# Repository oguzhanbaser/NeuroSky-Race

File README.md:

# NeuroSky-Race

### If you want to use STM32F103 with this project, you should choose "stm32" branch. 

In this application you can use your attention level to control car speed. Application designed for two racers. You will need following items for this project:

    - NeuroSky Mindwave Sensors * 2
    - Arduino (Nano in this example but can be different) * 2
    - IRFZ44N Mosfet * 2
    - HC-05 Bluetooth * 2
    - Slot Car Track
    - MZ-80 (Optional) * 2
    - FTDI Converter(Optional) * 2
    - PC (Optional)

### First-Upload
For the first UPLOAD you have to uncomment this line in "configuration.h". Next time you can comment it again. This line saves speed levels to EEPROM. 

```arduino

//#define WRITE_EEPROM 

```

### Interface
If you want to use NodeJs web interface you will need a PC to run server. Connect two Arduino with USB cable to PC and set port names in "server.js"

```javascript
var portName1 = "COM5";         //if you use using Linux /dev/tty***
var portName2 = "COM13";        //if you are using Linux /dev/tty***
```

```sh

$ cd Web-Interface
$ npm install
$ node server.js

```

</img>

### Software Serial
You can use FTDI converter or direct Arduino USB Plug to connect PC with Serial communication. You should uncomment this line in "configuration.h" and use A4 as RX, A5 as TX pin

```arduino

//#define USE_EXTERNAL_USB

```

## CARS WILL NOT MOVE IF .. !!
In this application if there are not two racers which are signal qualites equals zero(means max signal quality) cars cannot move. I needed this specification for race concept. If you want to disable it, comment this line in "configuration.h"

```arduino

#define MAKE_GAME

```

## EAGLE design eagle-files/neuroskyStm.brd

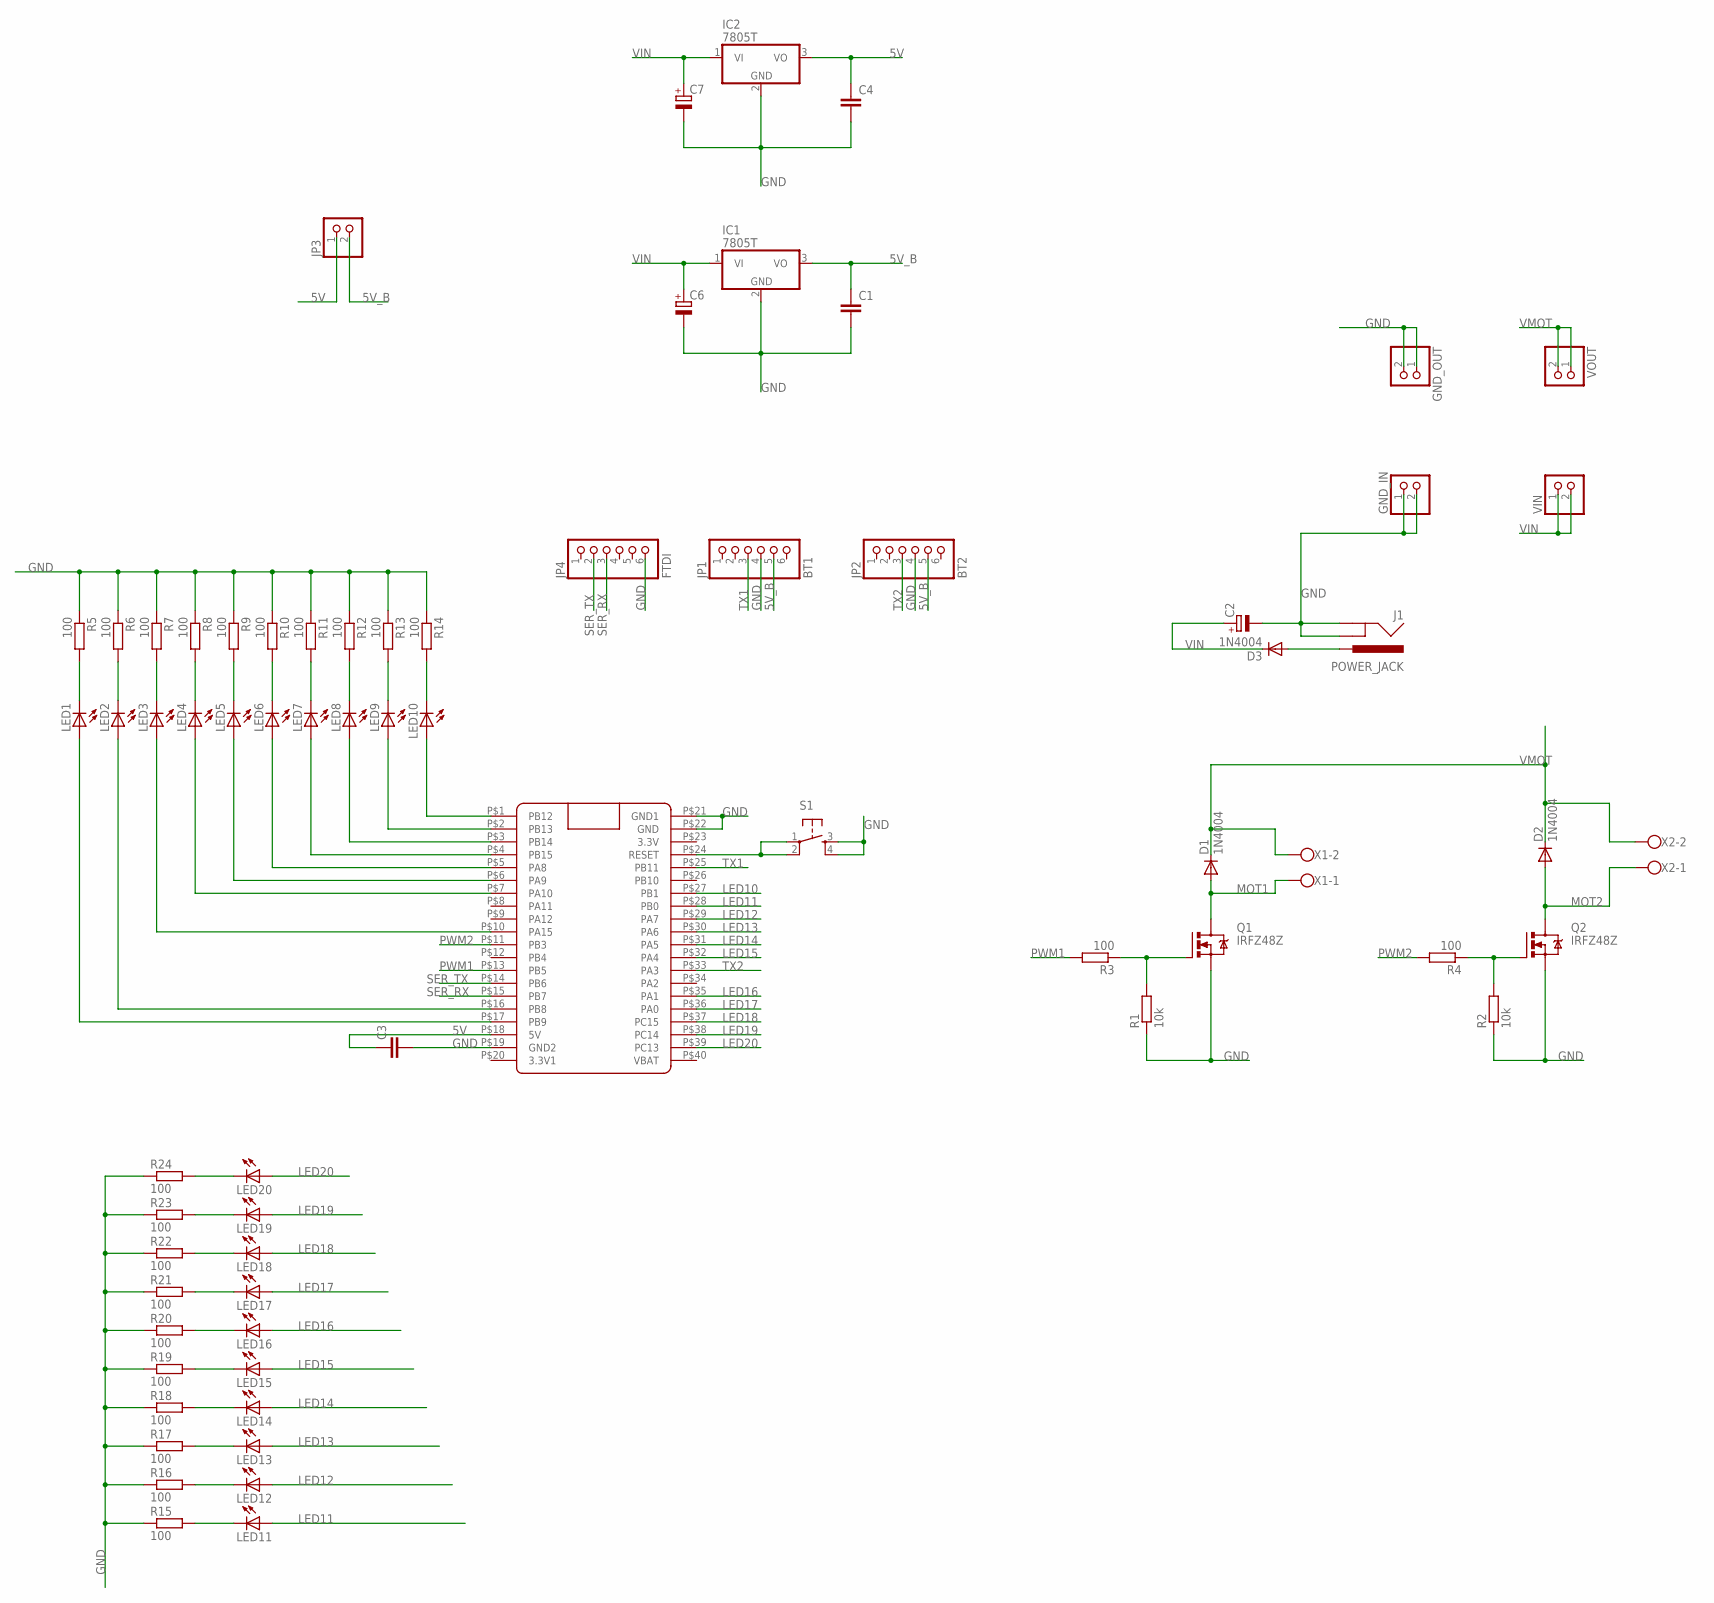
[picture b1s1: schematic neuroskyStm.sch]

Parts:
C1, C3, C4: C-EU050-035X075; C050-035X075
C2, C6, C7: CPOL-EUE3.5-8; E3,5-8
D1, D2, D3: 1N4004; DO41-10
GND_IN: PINHD-1X2; 1X02
GND_OUT: PINHD-1X2; 1X02
IC1, IC2: 7805T; TO220H
J1: POWER_JACK; POWER_JACK_PTH
JP1: BT1; 1X06
JP2: BT2; 1X06
JP3: PINHD-1X2; 1X02
JP4: FTDI; 1X06
LED1, LED2, LED3, LED4, LED5, LED6, LED7, LED8, LED9, LED10, LED11, LED12, LED13, LED14, LED15, LED16, LED17, LED18, LED19, LED20: LED5MM
Q1, Q2: IRFZ48Z; TO220BH
R1, R2: 10k; 0207/10
R3, R4, R5, R6, R7, R8, R9, R10, R11, R12, R13, R14, R15, R16, R17, R18, R19, R20, R21, R22, R23, R24: 100; 0207/10
S1: TAC_SWITCHPTH; TACTILE-PTH
U$1: BLUE_PILL
VIN: PINHD-1X2; 1X02
VOUT: PINHD-1X2; 1X02
X1, X2: W237-102

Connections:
5V: C3.1, C4.1, IC2.3 (VO), JP3.1, U$1.P$18 (5V)
5V_B: C1.1, IC1.3 (VO), JP1.5, JP2.5, JP3.2
GND: C1.2, C2.-, C3.2, C4.2, C6.-, C7.-, GND_IN.1, GND_IN.2, GND_OUT.1, GND_OUT.2, IC1.2 (GND), IC2.2 (GND), J1.GND, J1.GNDBREAK, JP1.4, JP2.4, JP4.6, Q1.S, Q2.S, R1.1, R2.1, R5.1, R6.1, R7.1, R8.1, R9.1, R10.1, R11.1, R12.1, R13.1, R14.1, R15.1, R16.1, R17.1, R18.1, R19.1, R20.1, R21.1, R22.1, R23.1, R24.1, S1.3, S1.4, U$1.P$19 (GND2), U$1.P$21 (GND1), U$1.P$22 (GND)
LED10: U$1.P$27 (PB1)
LED11: LED11.A, U$1.P$28 (PB0)
LED12: LED12.A, U$1.P$29 (PA7)
LED13: LED13.A, U$1.P$30 (PA6)
LED14: LED14.A, U$1.P$31 (PA5)
LED15: LED15.A, U$1.P$32 (PA4)
LED16: LED16.A, U$1.P$35 (PA1)
LED17: LED17.A, U$1.P$36 (PA0)
LED18: LED18.A, U$1.P$37 (PC15)
LED19: LED19.A, U$1.P$38 (PC14)
LED20: LED20.A, U$1.P$39 (PC13)
MOT1: D1.A, Q1.D, X1.1
MOT2: D2.A, Q2.D, X2.1
unnamed: D3.A, J1.PWR
unnamed: LED10.A, U$1.P$1 (PB12)
unnamed: LED9.A, U$1.P$2 (PB13)
unnamed: Q2.G, R2.2, R4.1
unnamed: LED8.A, U$1.P$3 (PB14)
unnamed: Q1.G, R1.2, R3.1
unnamed: LED7.A, U$1.P$4 (PB15)
unnamed: LED6.A, U$1.P$5 (PA8)
unnamed: LED5.A, U$1.P$6 (PA9)
unnamed: LED4.A, U$1.P$7 (PA10)
unnamed: LED3.A, U$1.P$10 (PA15)
unnamed: LED2.A, U$1.P$16 (PB8)
unnamed: LED1.A, U$1.P$17 (PB9)
unnamed: LED1.K (C), R5.2
unnamed: LED2.K (C), R6.2
unnamed: LED3.K (C), R7.2
unnamed: LED4.K (C), R8.2
unnamed: LED5.K (C), R9.2
unnamed: LED6.K (C), R10.2
unnamed: LED7.K (C), R11.2
unnamed: LED8.K (C), R12.2
unnamed: LED9.K (C), R13.2
unnamed: LED10.K (C), R14.2
unnamed: S1.1, S1.2, U$1.P$24 (RESET)
unnamed: LED11.K (C), R15.2
unnamed: LED12.K (C), R16.2
unnamed: LED13.K (C), R17.2
unnamed: LED14.K (C), R18.2
unnamed: LED15.K (C), R19.2
unnamed: LED16.K (C), R20.2
unnamed: LED17.K (C), R21.2
unnamed: LED18.K (C), R22.2
unnamed: LED19.K (C), R23.2
unnamed: LED20.K (C), R24.2
PWM1: R3.2, U$1.P$13 (PB5)
PWM2: R4.2, U$1.P$11 (PB3)
SER_RX: JP4.3, U$1.P$15 (PB7)
SER_TX: JP4.2, U$1.P$14 (PB6)
TX1: JP1.3, U$1.P$25 (PB11)
TX2: JP2.3, U$1.P$33 (PA3)
VIN: C2.+, C6.+, C7.+, D3.C, IC1.1 (VI), IC2.1 (VI), VIN.1, VIN.2
VMOT: D1.C, D2.C, VOUT.1, VOUT.2, X1.2, X2.2

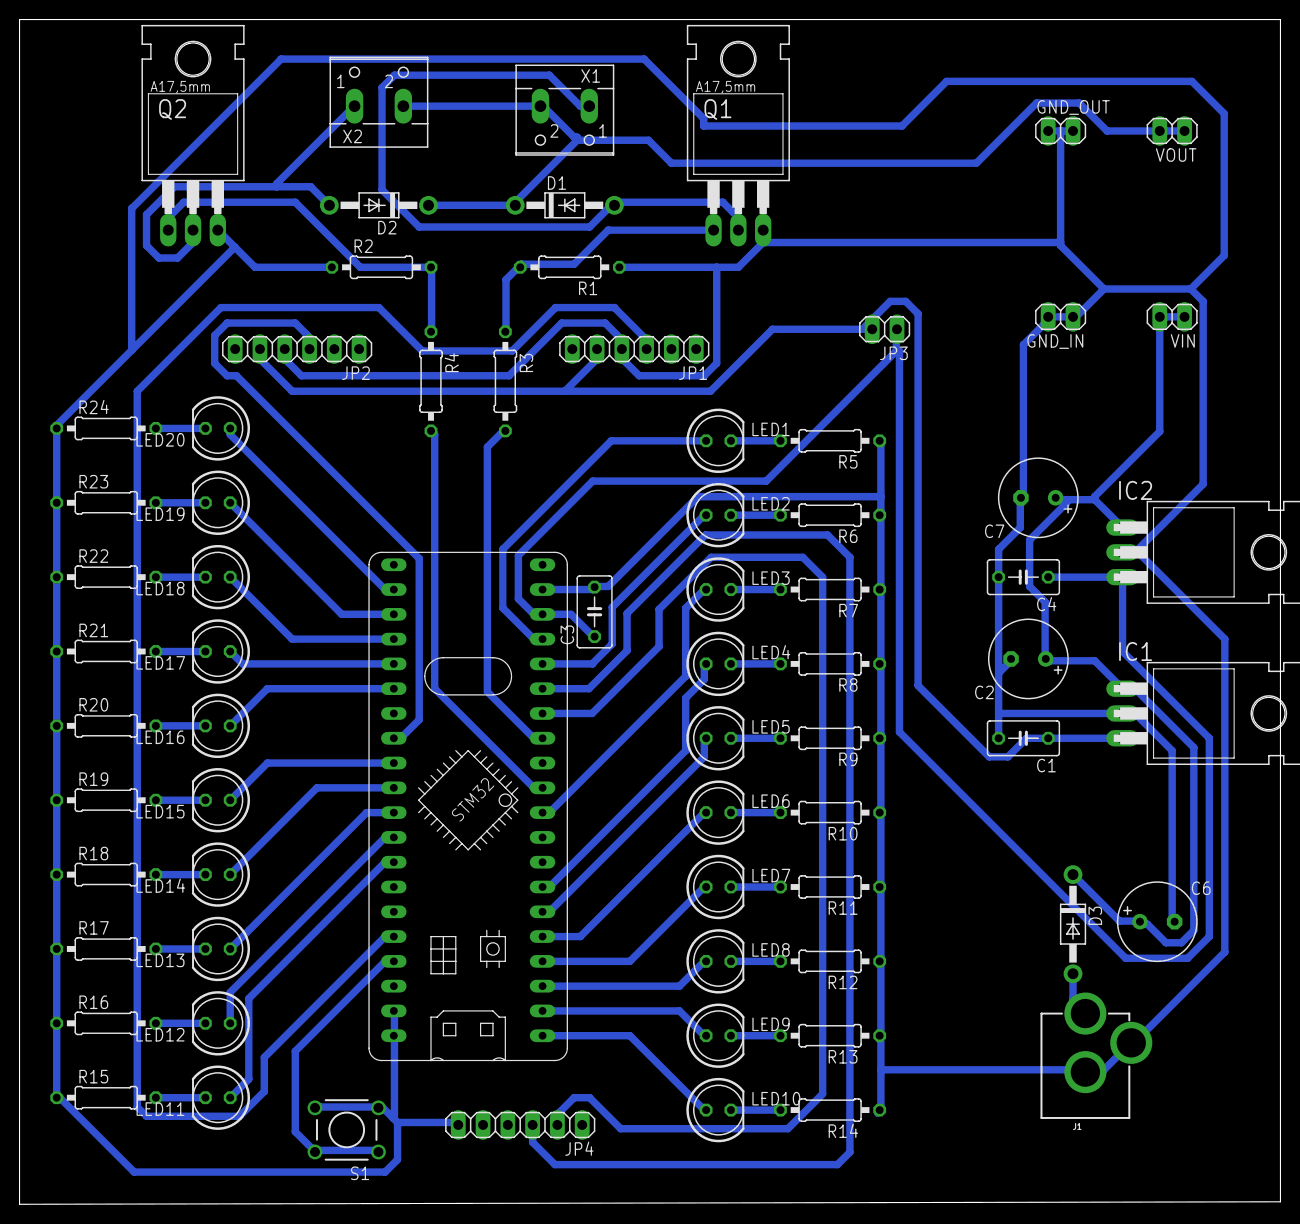
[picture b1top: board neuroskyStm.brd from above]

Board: 2 copper layers, 129.2 x 121.4 mm, 70 parts (0 on the bottom side), 57 nets.

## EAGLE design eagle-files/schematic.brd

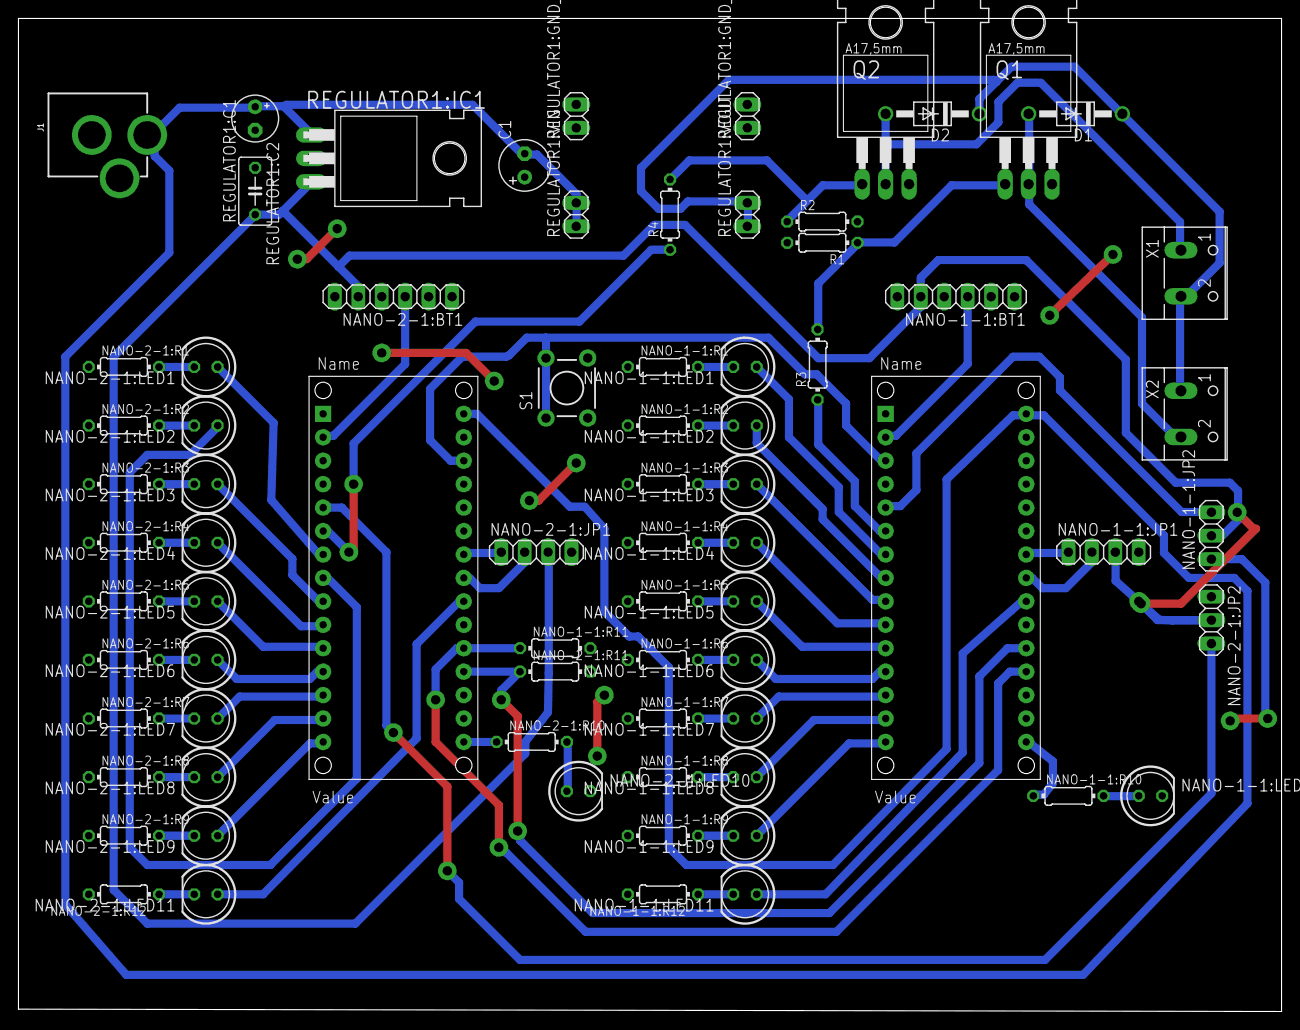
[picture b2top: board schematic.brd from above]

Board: 2 copper layers, 136.9 x 107.6 mm, 74 parts (0 on the bottom side), 65 nets.

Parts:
C1: E2,5-6
D1, D2: 1N4004; DO41-10
J1: POWER_JACK; POWER_JACK_PTH
NANO-1-1:BT1, NANO-2-1:BT1: 1X06
NANO-1-1:JP1, NANO-2-1:JP1: 1X04
NANO-1-1:JP2, NANO-2-1:JP2: 1X03
NANO-1-1:LED1, NANO-1-1:LED2, NANO-1-1:LED3, NANO-1-1:LED4, NANO-1-1:LED5, NANO-1-1:LED6, NANO-1-1:LED7, NANO-1-1:LED8, NANO-1-1:LED9, NANO-1-1:LED10, NANO-1-1:LED11, NANO-2-1:LED1, NANO-2-1:LED2, NANO-2-1:LED3, NANO-2-1:LED4, NANO-2-1:LED5, NANO-2-1:LED6, NANO-2-1:LED7, NANO-2-1:LED8, NANO-2-1:LED9, NANO-2-1:LED10, NANO-2-1:LED11: LED5MM
NANO-1-1:R1, NANO-1-1:R2, NANO-1-1:R3, NANO-1-1:R4, NANO-1-1:R5, NANO-1-1:R6, NANO-1-1:R7, NANO-1-1:R8, NANO-1-1:R9, NANO-1-1:R10, NANO-1-1:R12, NANO-2-1:R2, NANO-2-1:R3, NANO-2-1:R4, NANO-2-1:R5, NANO-2-1:R6, NANO-2-1:R7, NANO-2-1:R8, NANO-2-1:R9: 0204/7
NANO-1-1:R11, NANO-2-1:R11: 10k; 0204/7
NANO-1-1:U$1, NANO-2-1:U$1: ARDUINONANO; PDIP-32
NANO-2-1:R1, NANO-2-1:R10, NANO-2-1:R12: 220; 0204/7
Q1, Q2: IRFZ48Z; TO220BH
R1, R2: 2.2k; 0204/7
R3, R4: 100; 0204/7
REGULATOR1:C1: C050-035X075
REGULATOR1:C2: E2,5-5
REGULATOR1:GND_IN, REGULATOR1:GND_OUT, REGULATOR1:VIN, REGULATOR1:VOUT: 1X02
REGULATOR1:IC1: 7805T; TO220H
S1: TACTILE-PTH
X1, X2: W237-102

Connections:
6V: D1.C, D2.C, REGULATOR1:VOUT.1, REGULATOR1:VOUT.2, X1.2, X2.1
GND: C1.+, J1.GND, J1.GNDBREAK, NANO-1-1:BT1.4, NANO-1-1:JP1.4, NANO-1-1:JP2.1, NANO-1-1:LED10.K, NANO-1-1:R1.1, NANO-1-1:R2.1, NANO-1-1:R3.1, NANO-1-1:R4.1, NANO-1-1:R5.1, NANO-1-1:R6.1, NANO-1-1:R7.1, NANO-1-1:R8.1, NANO-1-1:R9.1, NANO-1-1:R11.2, NANO-1-1:R12.2, NANO-1-1:U$1.GND, NANO-1-1:U$1.GND1, NANO-2-1:BT1.4, NANO-2-1:JP1.4, NANO-2-1:JP2.1, NANO-2-1:LED10.K, NANO-2-1:R1.1, NANO-2-1:R2.1, NANO-2-1:R3.1, NANO-2-1:R4.1, NANO-2-1:R5.1, NANO-2-1:R6.1, NANO-2-1:R7.1, NANO-2-1:R8.1, NANO-2-1:R9.1, NANO-2-1:R11.2, NANO-2-1:R12.2, NANO-2-1:U$1.GND, NANO-2-1:U$1.GND1, Q1.S, Q2.S, R1.2, R2.2, REGULATOR1:C1.2, REGULATOR1:C2.-, REGULATOR1:GND_IN.1, REGULATOR1:GND_IN.2, REGULATOR1:GND_OUT.1, REGULATOR1:GND_OUT.2, REGULATOR1:IC1.2, S1.3, S1.4
unnamed: Q1.G, R1.1, R3.2
unnamed: NANO-1-1:U$1.A6, NANO-2-1:R11.1, NANO-2-1:U$1.A7
unnamed: NANO-2-1:U$1.D3, R4.1
unnamed: NANO-1-1:R11.1, NANO-1-1:U$1.A7, NANO-2-1:U$1.A6
unnamed: D1.A, Q1.D, X2.2
unnamed: D2.A, Q2.D, X1.1
unnamed: NANO-1-1:U$1.D3, R3.1
unnamed: Q2.G, R2.1, R4.2
unnamed: NANO-1-1:U$1.RESET, NANO-2-1:U$1.RESET1, S1.1, S1.2
NANO-1-1:BT-TX: NANO-1-1:BT1.3, NANO-1-1:U$1.D0/RX
NANO-1-1:N$1: NANO-1-1:LED9.A, NANO-1-1:U$1.D12
NANO-1-1:N$2: NANO-1-1:LED8.A, NANO-1-1:U$1.D11
NANO-1-1:N$3: NANO-1-1:LED7.A, NANO-1-1:U$1.D10
NANO-1-1:N$4: NANO-1-1:LED6.A, NANO-1-1:U$1.D9
NANO-1-1:N$5: NANO-1-1:LED5.A, NANO-1-1:U$1.D8
NANO-1-1:N$6: NANO-1-1:LED4.A, NANO-1-1:U$1.D7
NANO-1-1:N$7: NANO-1-1:LED3.A, NANO-1-1:U$1.D6
NANO-1-1:N$8: NANO-1-1:LED2.A, NANO-1-1:U$1.D5
NANO-1-1:N$9: NANO-1-1:LED1.A, NANO-1-1:U$1.D4
NANO-1-1:N$10: NANO-1-1:R10.1, NANO-1-1:U$1.D13
NANO-1-1:N$11: NANO-1-1:LED1.K, NANO-1-1:R1.2
NANO-1-1:N$12: NANO-1-1:LED2.K, NANO-1-1:R2.2
NANO-1-1:N$13: NANO-1-1:LED3.K, NANO-1-1:R3.2
NANO-1-1:N$14: NANO-1-1:LED4.K, NANO-1-1:R4.2
NANO-1-1:N$15: NANO-1-1:LED5.K, NANO-1-1:R5.2
NANO-1-1:N$16: NANO-1-1:LED6.K, NANO-1-1:R6.2
NANO-1-1:N$17: NANO-1-1:LED7.K, NANO-1-1:R7.2
NANO-1-1:N$18: NANO-1-1:LED8.K, NANO-1-1:R8.2
NANO-1-1:N$19: NANO-1-1:LED9.K, NANO-1-1:R9.2
NANO-1-1:N$20: NANO-1-1:LED11.A, NANO-1-1:U$1.A4
NANO-1-1:N$21: NANO-1-1:LED11.K, NANO-1-1:R12.1
NANO-1-1:N$22: NANO-1-1:LED10.A, NANO-1-1:R10.2
NANO-1-1:N$23: NANO-1-1:JP1.1, NANO-1-1:U$1.A2
NANO-1-1:N$24: NANO-1-1:JP1.2, NANO-1-1:U$1.A3
NANO-1-1:N$25: NANO-1-1:JP2.3, NANO-1-1:U$1.D2
NANO-2-1:BT-TX: NANO-2-1:BT1.3, NANO-2-1:U$1.D0/RX
NANO-2-1:N$1: NANO-2-1:LED9.A, NANO-2-1:U$1.D12
NANO-2-1:N$2: NANO-2-1:LED8.A, NANO-2-1:U$1.D11
NANO-2-1:N$3: NANO-2-1:LED7.A, NANO-2-1:U$1.D10
NANO-2-1:N$4: NANO-2-1:LED6.A, NANO-2-1:U$1.D9
NANO-2-1:N$5: NANO-2-1:LED5.A, NANO-2-1:U$1.D8
NANO-2-1:N$6: NANO-2-1:LED4.A, NANO-2-1:U$1.D7
NANO-2-1:N$7: NANO-2-1:LED3.A, NANO-2-1:U$1.D6
NANO-2-1:N$8: NANO-2-1:LED2.A, NANO-2-1:U$1.D5
NANO-2-1:N$9: NANO-2-1:LED1.A, NANO-2-1:U$1.D4
NANO-2-1:N$10: NANO-2-1:LED11.K, NANO-2-1:R12.1
NANO-2-1:N$11: NANO-2-1:LED1.K, NANO-2-1:R1.2
NANO-2-1:N$12: NANO-2-1:LED2.K, NANO-2-1:R2.2
NANO-2-1:N$13: NANO-2-1:LED3.K, NANO-2-1:R3.2
NANO-2-1:N$14: NANO-2-1:LED4.K, NANO-2-1:R4.2
NANO-2-1:N$15: NANO-2-1:LED5.K, NANO-2-1:R5.2
NANO-2-1:N$16: NANO-2-1:LED6.K, NANO-2-1:R6.2
NANO-2-1:N$17: NANO-2-1:LED7.K, NANO-2-1:R7.2
NANO-2-1:N$18: NANO-2-1:LED8.K, NANO-2-1:R8.2
NANO-2-1:N$19: NANO-2-1:LED9.K, NANO-2-1:R9.2
NANO-2-1:N$20: NANO-2-1:LED11.A, NANO-2-1:U$1.A4
NANO-2-1:N$21: NANO-2-1:R10.1, NANO-2-1:U$1.D13
NANO-2-1:N$22: NANO-2-1:LED10.A, NANO-2-1:R10.2
NANO-2-1:N$23: NANO-2-1:JP1.1, NANO-2-1:U$1.A2
NANO-2-1:N$24: NANO-2-1:JP1.2, NANO-2-1:U$1.A3
NANO-2-1:N$25: NANO-2-1:JP2.3, NANO-2-1:U$1.D2
SENS_VOUT: NANO-1-1:BT1.5, NANO-1-1:JP1.3, NANO-1-1:JP2.2, NANO-2-1:BT1.5, NANO-2-1:JP1.3, NANO-2-1:JP2.2, REGULATOR1:C1.1, REGULATOR1:IC1.3
VIN: C1.-, J1.PWR, NANO-1-1:U$1.VIN, NANO-2-1:U$1.VIN, REGULATOR1:C2.+, REGULATOR1:IC1.1, REGULATOR1:VIN.1, REGULATOR1:VIN.2

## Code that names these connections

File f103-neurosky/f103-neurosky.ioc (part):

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Mcu.Name=STM32F103C(8-B)Tx
Mcu.Package=LQFP48
Mcu.UserName=STM32F103C8Tx
PA0-WKUP.GPIOParameters=GPIO_Label
PA0-WKUP.GPIO_Label=LED17
PA0-WKUP.Signal=GPIO_Output
PA1.GPIOParameters=GPIO_Label
PA1.GPIO_Label=LED16
PA1.Signal=GPIO_Output
PA10.GPIOParameters=GPIO_Label
PA10.GPIO_Label=LED4
PA10.Signal=GPIO_Output
PA11.Mode=Device
PA11.Signal=USB_DM
PA12.Mode=Device
PA12.Signal=USB_DP
PA13.Mode=Serial_Wire
PA13.Signal=SYS_JTMS-SWDIO
PA14.Mode=Serial_Wire
PA14.Signal=SYS_JTCK-SWCLK
PA15.GPIOParameters=GPIO_Label
PA15.GPIO_Label=LED3
PA15.Signal=GPIO_Output
PA2.Mode=Asynchronous
PA2.Signal=USART2_TX
PA3.Mode=Asynchronous
PA3.Signal=USART2_RX
PA4.GPIOParameters=GPIO_Label
PA4.GPIO_Label=LED15
PA4.Signal=GPIO_Output
PA5.GPIOParameters=GPIO_Label
PA5.GPIO_Label=LED14
PA5.Signal=GPIO_Output
PA6.GPIOParameters=GPIO_Label
PA6.GPIO_Label=LED13
PA6.Signal=GPIO_Output
PA7.GPIOParameters=GPIO_Label
PA7.GPIO_Label=LED12
PA7.Signal=GPIO_Output
PA8.GPIOParameters=GPIO_Label
PA8.GPIO_Label=LED6
PA8.Signal=GPIO_Output
PA9.GPIOParameters=GPIO_Label
PA9.GPIO_Label=LED5
PA9.Signal=GPIO_Output
PB0.GPIOParameters=GPIO_Label
PB0.GPIO_Label=LED11
PB0.Signal=GPIO_Output
PB10.Mode=Asynchronous
PB10.Signal=USART3_TX
PB11.Mode=Asynchronous
PB11.Signal=USART3_RX
PB12.GPIOParameters=GPIO_Label
PB12.GPIO_Label=LED10
PB12.Signal=GPIO_Output
PB13.GPIOParameters=GPIO_Label
PB13.GPIO_Label=LED9
PB13.Signal=GPIO_Output
PB14.GPIOParameters=GPIO_Label
PB14.GPIO_Label=LED8
PB14.Signal=GPIO_Output
PB15.GPIOParameters=GPIO_Label
PB15.GPIO_Label=LED7
PB15.Signal=GPIO_Output
PB3.Signal=S_TIM2_CH2
PB5.Signal=S_TIM3_CH2
PB8.GPIOParameters=GPIO_Label
PB8.GPIO_Label=LED2
PB8.Signal=GPIO_Output
PB9.GPIOParameters=GPIO_Label
PB9.GPIO_Label=LED1
PB9.Signal=GPIO_Output
PC13-TAMPER-RTC.GPIOParameters=GPIO_Label
PC13-TAMPER-RTC.GPIO_Label=LED20
PC13-TAMPER-RTC.Signal=GPIO_Output
PC14-OSC32_IN.GPIOParameters=GPIO_Label
PC14-OSC32_IN.GPIO_Label=LED19
PC14-OSC32_IN.Signal=GPIO_Output
PC15-OSC32_OUT.GPIOParameters=GPIO_Label
PC15-OSC32_OUT.GPIO_Label=LED18
PC15-OSC32_OUT.Signal=GPIO_Output
PD0-OSC_IN.Mode=HSE-External-Oscillator
PD0-OSC_IN.Signal=RCC_OSC_IN
PD1-OSC_OUT.Mode=HSE-External-Oscillator
PD1-OSC_OUT.Signal=RCC_OSC_OUT
RCC.SYSCLKFreq_VALUE=72000000
RCC.SYSCLKSource=RCC_SYSCLKSOURCE_PLLCLK
board=custom

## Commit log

2017-05-25 files
2017-05-25 we files
2017-05-25 readme
2017-06-18 schematics
2019-04-11 stm32-code
2021-10-04 update packages
2021-10-05 some changes
2021-11-01 readme stm32
2022-08-01 update levels

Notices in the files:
parts and their libraries:
SparkFun-Connectors: Licensing: Creative Commons ShareAlike 4.0 International - https://creativecommons.org/licenses/by-sa/4.0
